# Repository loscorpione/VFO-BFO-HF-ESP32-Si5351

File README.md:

<h2 align="center">VFO/BFO con SI5351A ed ESP32</h2>

VFO & BFO con Si5351 gestito da ESP32 DevKit V1 per la gamma di frequenze HF, da 1 a 30 MHz.

## 📺 Video del progetto

<p align="center">
  
</p>

## 📋 Caratteristiche principali

- Generazione VFO e BFO indipendenti con SI5351A
- Gestione modi: AM, LSB, USB, CW
- Controllo AGC (Fast/Slow) e attenuatore (-20dB)
- Pitch BFO regolabile (±300 Hz, step 5 Hz)
- S-meter digitale con memoria di picco
- Supporto encoder ottico (400 PPR) e meccanico (24 PPR)
- Display TFT a colori (TFT_eSPI)
- Tastiera a matrice 4x4 via PCF8574T per inserimento frequenza
- Espansione I/O tramite PCF8574 (8 bit)
- Memorizzazione configurazioni su EEPROM 24LC256 (32KB)
- Firmware modulare in C++
- Calibrazione SI5351 automatica e manuale

## ✨ Novità della versione 2.1.0

Questa release introduce miglioramenti significativi nella gestione della frequenza, nell'interfaccia utente e nella calibrazione.

### 🎯 Frequenza visualizzata sempre corretta
- **IF dinamica per modalità**: la frequenza del VFO viene calcolata dinamicamente in base alla modalità selezionata (AM, LSB, USB, CW), compensando l'offset del BFO.
- **Display allineato alla stazione reale**: la frequenza mostrata sul display corrisponde sempre a quella effettiva della stazione ricevuta, senza scostamenti di 1.5 kHz.
- **Confronto diretto con altri ricevitori**: ora è possibile confrontare la frequenza visualizzata con quella di un IC-756 o di un altro apparato commerciale.

### 📻 Cambio automatico della banda laterale
- **LSB sotto 10 MHz, USB sopra 10 MHz**: al cambio banda, la modalità viene impostata automaticamente in base alla frequenza.
- **Funziona con tutte le fonti**: il cambio automatico si attiva sia cambiando banda, sia ruotando l'encoder, sia inserendo la frequenza da tastiera.
- **Rispetto delle modalità AM e CW**: se l'utente ha selezionato AM o CW, il cambio automatico non viene applicato.

### ⌨️ Miglioramenti alla tastiera 4x4
- **Limiti sui tasti `*` e `#`**: il cambio step si ferma ai limiti minimo (10 Hz) e massimo (10 kHz), evitando valori non validi.
- **Inserimento frequenza più intuitivo**: i punti separatori vengono aggiunti automaticamente dopo la 2ª e la 5ª cifra.
- **Timeout con ripristino corretto**: dopo 5 secondi di inattività, il display torna alla frequenza corrente senza lasciare la modalità input.

### 🖥️ Nuova schermata iniziale
- **Logo e informazioni di sistema**: la schermata iniziale mostra logo, versione hardware, versione firmware, autore e lista dei dispositivi I2C rilevati.
- **Rilevamento automatico EEPROM**: il sistema identifica il tipo di EEPROM (24LC32, 24LC64, 24LC128, 24LC256) in base alla dimensione configurata.

### 🔧 Calibrazione SI5351 migliorata
- **Calibrazione automatica con `CAL_FREQ`**: inserendo la frequenza misurata con un frequenzimetro, il sistema calcola e applica il fattore di correzione ottimale.
- **Calibrazione manuale con `CAL_MAN`**: per utenti esperti, è possibile impostare direttamente il fattore di correzione.
- **Istruzioni integrate**: i comandi `CAL_MAN?` e `CAL_FREQ?` mostrano le procedure passo-passo.
- **Maggiore precisione ad alta frequenza**: la calibrazione è più efficace se eseguita su frequenze elevate (es. 28 MHz).

### 🐛 Bugfix e miglioramenti
- Corretto il disallineamento di 1.5 kHz tra frequenza visualizzata e frequenza reale in LSB/USB.
- Risolto il problema del font che rimaneva ingrandito dopo un errore di inserimento frequenza.
- Corretto il salvataggio della frequenza inserita da tastiera in EEPROM.
- Migliorata la stabilità della comunicazione I2C con la EEPROM esterna.
- Rimossi i messaggi di debug ridondanti dal monitor seriale.

## 🔧 Comandi

| Comando | Descrizione |
|---------|-------------|
| **Encoder VFO** | Selezione frequenza (step 10Hz, 100Hz, 1kHz, 10kHz) |
| **Encoder BFO** | Regolazione pitch BFO (±300Hz) |
| **STEP** | Cambio step VFO |
| **BAND** | Selezione banda (160m → 10m) |
| **MODE** | Selezione demodulazione (AM/LSB/USB/CW) |
| **AGC** | Fast / Slow |
| **ATT** | Attenuatore -20dB ON/OFF |
| **Tastiera 4x4** | Inserimento diretto frequenza (0-9, A=conferma, C/#=annulla) |
| **Tasti `*` e `#`** | Step down / Step up (con limiti 10Hz-10kHz) |

## 🖥️ Comandi seriali

| Comando | Descrizione |
|---------|-------------|
| `CAL_MAN <valore>` | Imposta fattore di calibrazione manuale |
| `CAL_MAN?` | Istruzioni per la calibrazione manuale |
| `CAL_FREQ <freq>` | Calibrazione automatica (inserisci frequenza misurata) |
| `CAL_FREQ?` | Istruzioni per la calibrazione automatica |
| `CAL_READ` | Legge il fattore di calibrazione corrente |
| `CAL_RESET` | Resetta la calibrazione a 0 |
| `INFO` | Mostra informazioni di sistema |
| `HELP` | Mostra tutti i comandi disponibili |

### Esempio di calibrazione automatica

```text
> CAL_FREQ 28454710

=== CALIBRAZIONE AUTOMATICA ===
Target: 28455000 Hz
Misurato: 28454710 Hz
Errore: -290 Hz
Fattore calcolato: -10193
✅ Calibrazione automatica salvata.
```

🎬 **Guarda il video dimostrativo:**

<p align="center">
  
</p>

## 🛠️ Architettura del codice
```text
VFO-BFO HF ESP32 Code/
├── src/
│ ├── main.cpp # Loop principale e gestione comandi seriale
│ ├── config.h # Pin, parametri e versioni
│ ├── display.cpp/h # Gestione display TFT e splash screen
│ ├── VFO_BFO.cpp/h # Gestione encoder VFO/BFO
│ ├── PLL.cpp/h # Configurazione SI5351
│ ├── bands.cpp/h # Gestione bande
│ ├── modes.cpp/h # Gestione modalità (AM/LSB/USB/CW)
│ ├── DigiOUT.cpp/h # Uscite digitali PCF8574
│ ├── s_meter.cpp/h # S-meter analogico
│ ├── functions.cpp/h # Gestione pulsanti AGC/ATT
│ ├── keypad.cpp/h # Gestione tastiera 4x4
│ └── EEPROM_manager.cpp/h # Memorizzazione configurazioni
└── platformio.ini # Configurazione PlatformIO
```

## 🔌 Collegamenti principali
```text
| Componente | Pin ESP32 |
|------------|-----------|
| VFO Encoder CLK | 34 |
| VFO Encoder DT | 35 |
| BFO Encoder CLK | 12 |
| BFO Encoder DT | 13 |
| STEP | 32 |
| BAND | 33 |
| MODE | 25 |
| AGC | 26 |
| ATT | 27 |
| I2C SDA | 21 |
| I2C SCL | 22 |
| S-Meter | 15 (ADC) |
```

## 📦 Dipendenze (platformio.ini)
```text
lib_deps = 
    bodmer/TFT_eSPI@^2.5.0
    madhephaestus/ESP32Encoder@^0.12.0
    robtillaart/PCF8574@^0.4.4
    robtillaart/I2CKeyPad@^0.5.2
```
## 📜 Licenza

MIT

## 👤 Autore

Scorpione Maker - IV3LDJ

GitHub: loscorpione

YouTube: @ScorpioneMaker

## ⭐ Se questo progetto ti è utile, lascia una stella su GitHub!

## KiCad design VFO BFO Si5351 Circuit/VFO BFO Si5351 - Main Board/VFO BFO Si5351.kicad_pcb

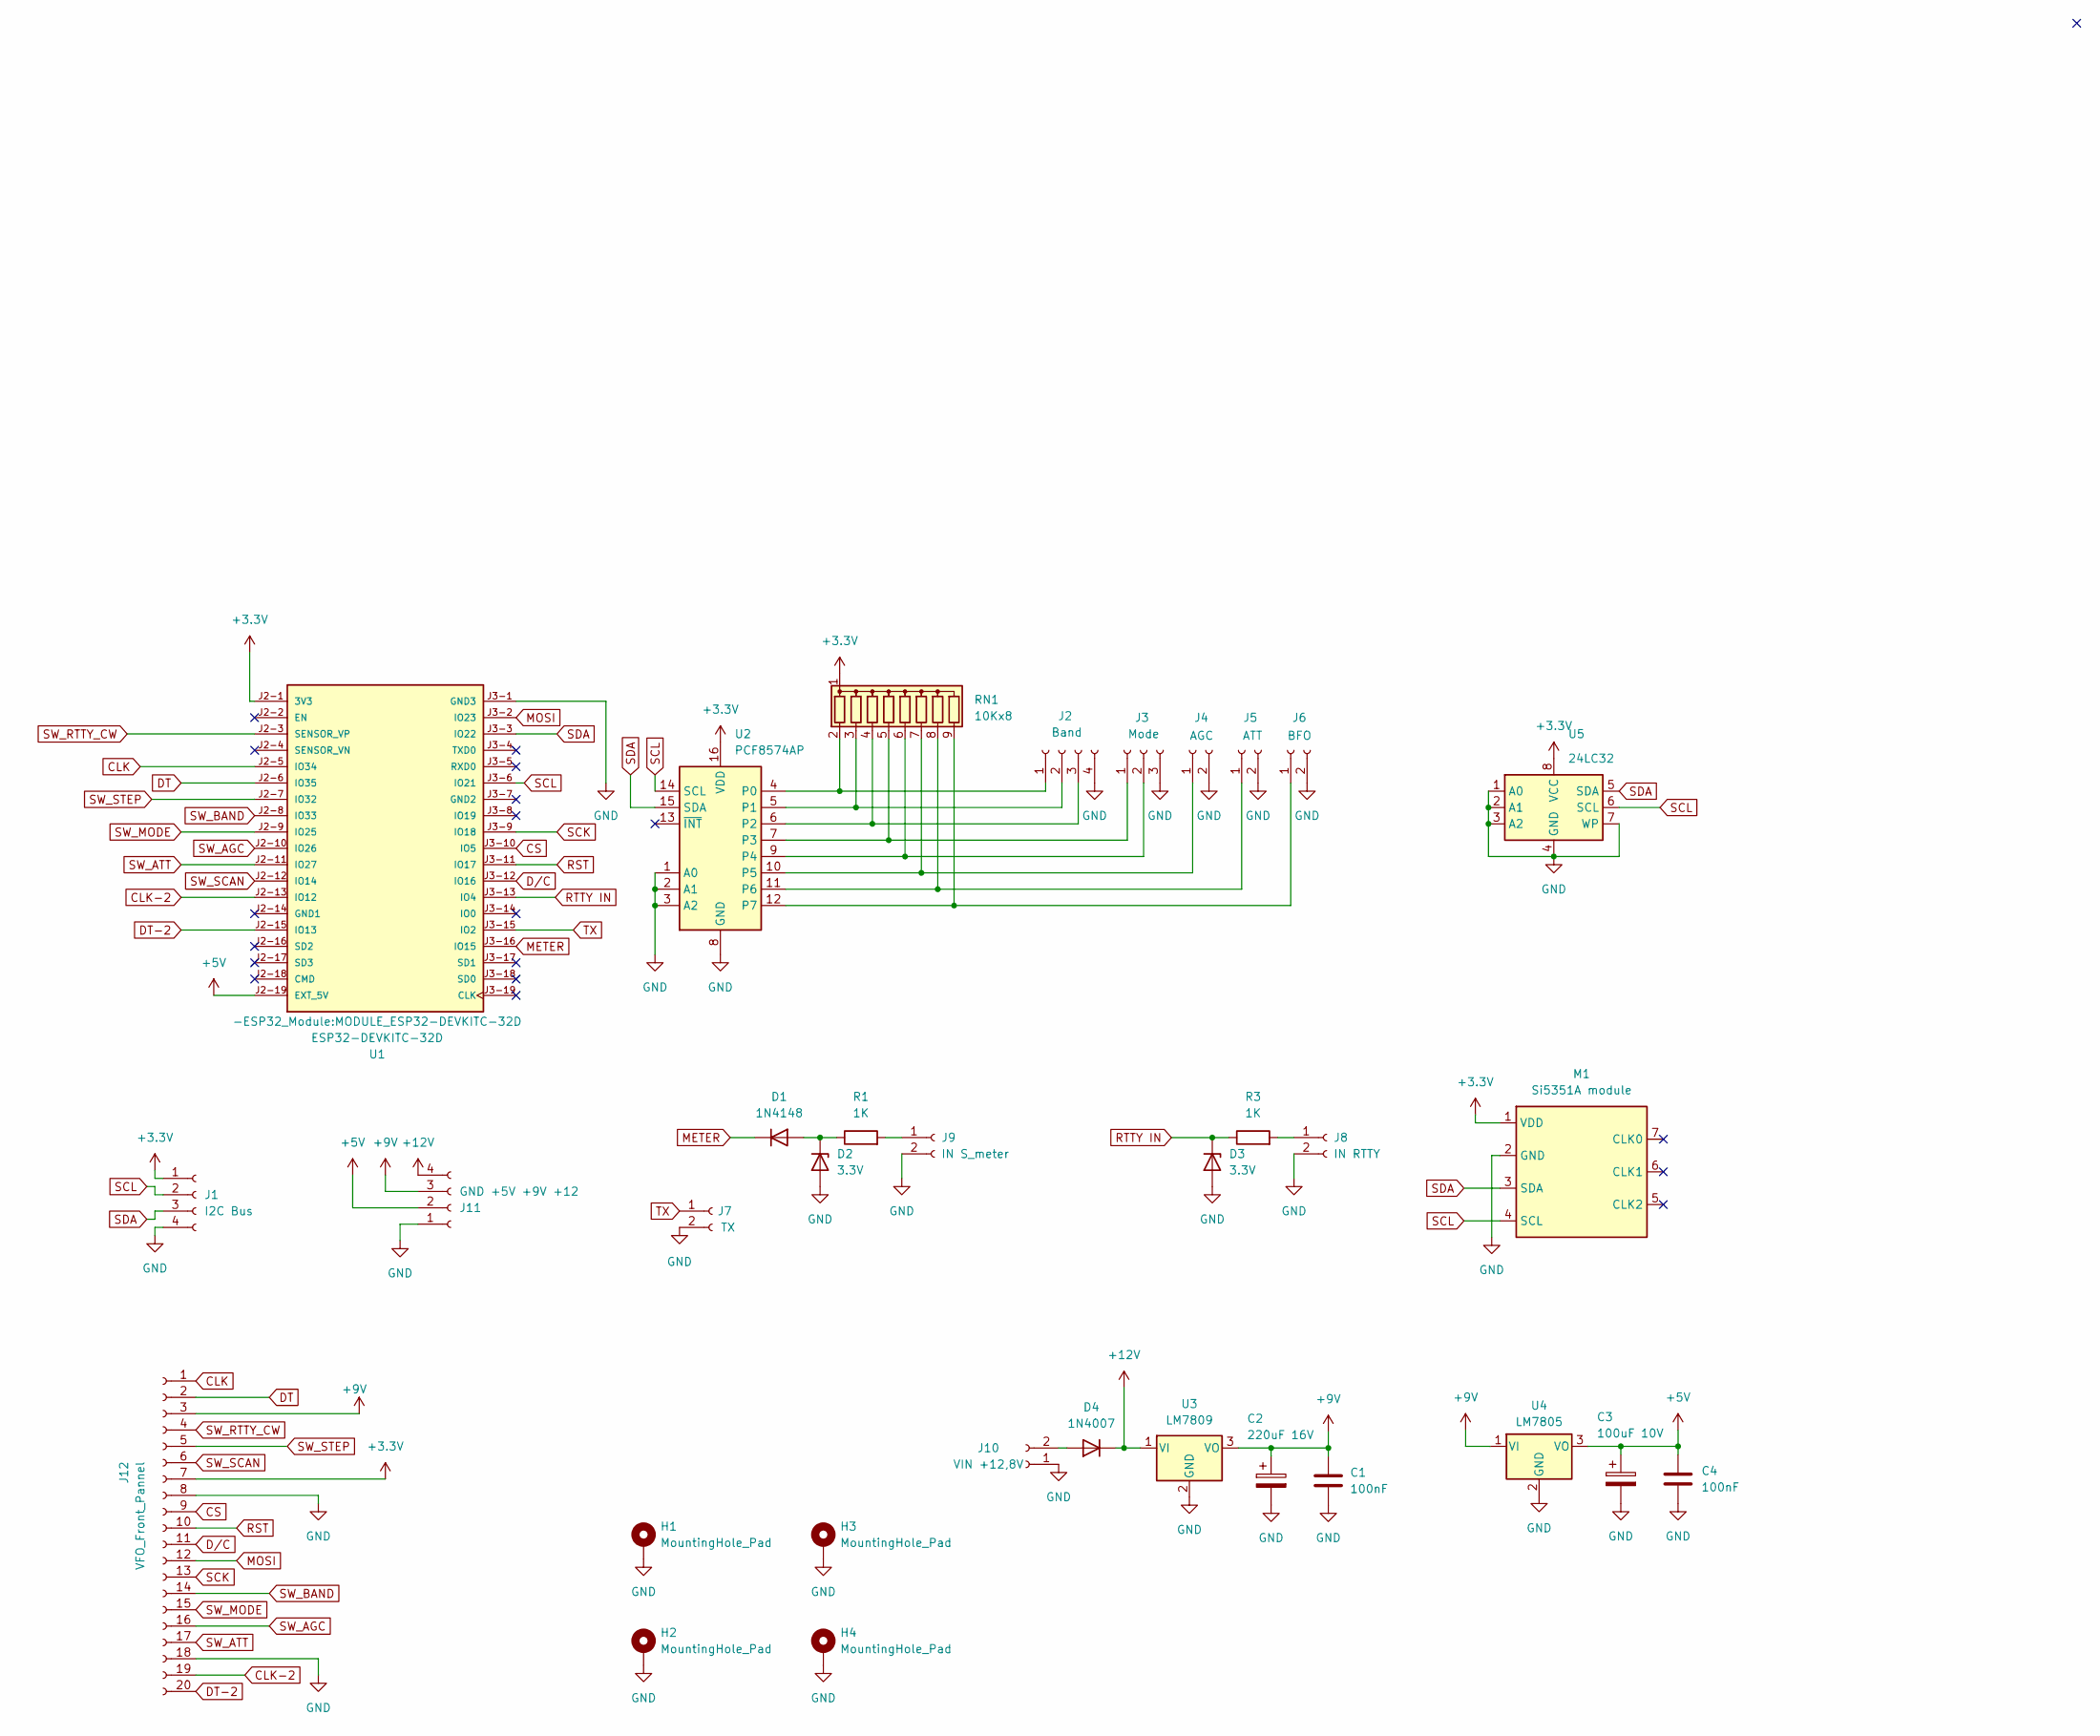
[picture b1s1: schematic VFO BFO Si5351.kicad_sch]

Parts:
C1, C4: 100nF; C_Rect_L7.0mm_W2.5mm_P5.00mm
C2: 220uF 16V; CP_Radial_D6.3mm_P2.50mm
C3: 100uF 10V; CP_Radial_D5.0mm_P2.00mm
D1: 1N4148; D_DO-35_SOD27_P7.62mm_Horizontal
D2, D3: 3.3V; D_DO-35_SOD27_P7.62mm_Horizontal
D4: 1N4007; D_DO-41_SOD81_P10.16mm_Horizontal
H1, H2, H3, H4: MountingHole_Pad; MountingHole_3.2mm_M3_DIN965_Pad_TopBottom
J1: I2C Bus; JST_EH_B4B-EH-A_1x04_P2.50mm_Vertical
J2: Band; JST_EH_B4B-EH-A_1x04_P2.50mm_Vertical
J3: Mode; JST_EH_B3B-EH-A_1x03_P2.50mm_Vertical
J4: AGC; JST_EH_B2B-EH-A_1x02_P2.50mm_Vertical
J5: ATT; JST_EH_B2B-EH-A_1x02_P2.50mm_Vertical
J6: BFO; JST_EH_B2B-EH-A_1x02_P2.50mm_Vertical
J7: TX; JST_EH_B2B-EH-A_1x02_P2.50mm_Vertical
J8: IN RTTY; JST_EH_B2B-EH-A_1x02_P2.50mm_Vertical
J9: IN S_meter; JST_EH_B2B-EH-A_1x02_P2.50mm_Vertical
J10: VIN +12,8V; JST_EH_B2B-EH-A_1x02_P2.50mm_Vertical
J11: GND +5V +9V +12; JST_EH_B4B-EH-A_1x04_P2.50mm_Vertical
J12: VFO_Front_Pannel; PinHeader_1x20_P2.54mm_Vertical
M1: Si5351A module; si5351a_Module
R1, R3: 1K; R_Axial_DIN0207_L6.3mm_D2.5mm_P10.16mm_Horizontal
RN1: 10Kx8; R_Array_SIP9
U1: ESP32-DEVKITC-32D; MODULE_ESP32-DEVKITC-32D; PARTREV V4
U2: PCF8574AP; DIP-16_W7.62mm
U3: LM7809; TO-220-3_Vertical
U4: LM7805; TO-220-3_Vertical
U5: 24LC32; DIP-8_W7.62mm

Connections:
+3.3V: J1.1, J12.7, M1.1 (VDD), RN1.1 (common), U1.J2-1 (3V3), U2.16 (VDD), U5.8 (VCC)
+5V: C3.1, C4.1, J11.2, U1.J2-19 (EXT_5V), U4.3 (VO)
+9V: C1.1, C2.1, J11.3, J12.3, U3.3 (VO), U4.1 (VI)
+12V: D4.1 (K), J11.4, U3.1 (VI)
CLK: J12.1, U1.J2-5 (IO34)
CLK-2: J12.19, U1.J2-13 (IO12)
CS: J12.9, U1.J3-10 (IO5)
DT: J12.2, U1.J2-6 (IO35)
DT-2: J12.20, U1.J2-15 (IO13)
D/C: J12.11, U1.J3-12 (IO16)
GND: C1.2, C2.2, C3.2, C4.2, D2.2 (A), D3.2 (A), H1.1, H2.1, H3.1, H4.1, J1.4, J2.4, J3.3, J4.2, J5.2, J6.2, J7.2, J8.2, J9.2, J10.1, J11.1, J12.8, J12.18, M1.2 (GND), U1.J3-1 (GND3), U2.1 (A0), U2.2 (A1), U2.3 (A2), U2.8 (GND), U3.2 (GND), U4.2 (GND), U5.1 (A0), U5.2 (A1), U5.3 (A2), U5.4 (GND), U5.7 (WP)
METER: D1.1 (K), U1.J3-16 (IO15)
MOSI: J12.12, U1.J3-2 (IO23)
unnamed: D1.2 (A), D2.1 (K), R1.1
unnamed: D4.2 (A), J10.2
unnamed: J2.1, RN1.2 (R1), U2.4 (P0)
unnamed: J2.2, RN1.3 (R2), U2.5 (P1)
unnamed: J2.3, RN1.4 (R3), U2.6 (P2)
unnamed: J3.1, RN1.5 (R4), U2.7 (P3)
unnamed: J3.2, RN1.6 (R5), U2.9 (P4)
unnamed: J4.1, RN1.7 (R6), U2.10 (P5)
unnamed: J5.1, RN1.8 (R7), U2.11 (P6)
unnamed: J6.1, RN1.9 (R8), U2.12 (P7)
unnamed: J8.1, R3.2
unnamed: J9.1, R1.2
RST: J12.10, U1.J3-11 (IO17)
RTTY IN: D3.1 (K), R3.1, U1.J3-13 (IO4)
SCK: J12.13, U1.J3-9 (IO18)
SCL: J1.2, M1.4 (SCL), U1.J3-6 (IO21), U2.14 (SCL), U5.6 (SCL)
SDA: J1.3, M1.3 (SDA), U1.J3-3 (IO22), U2.15 (SDA), U5.5 (SDA)
SW_AGC: J12.16, U1.J2-10 (IO26)
SW_ATT: J12.17, U1.J2-11 (IO27)
SW_BAND: J12.14, U1.J2-8 (IO33)
SW_MODE: J12.15, U1.J2-9 (IO25)
SW_RTTY_CW: J12.4, U1.J2-3 (SENSOR_VP)
SW_SCAN: J12.6, U1.J2-12 (IO14)
SW_STEP: J12.5, U1.J2-7 (IO32)
TX: J7.1, U1.J3-15 (IO2)

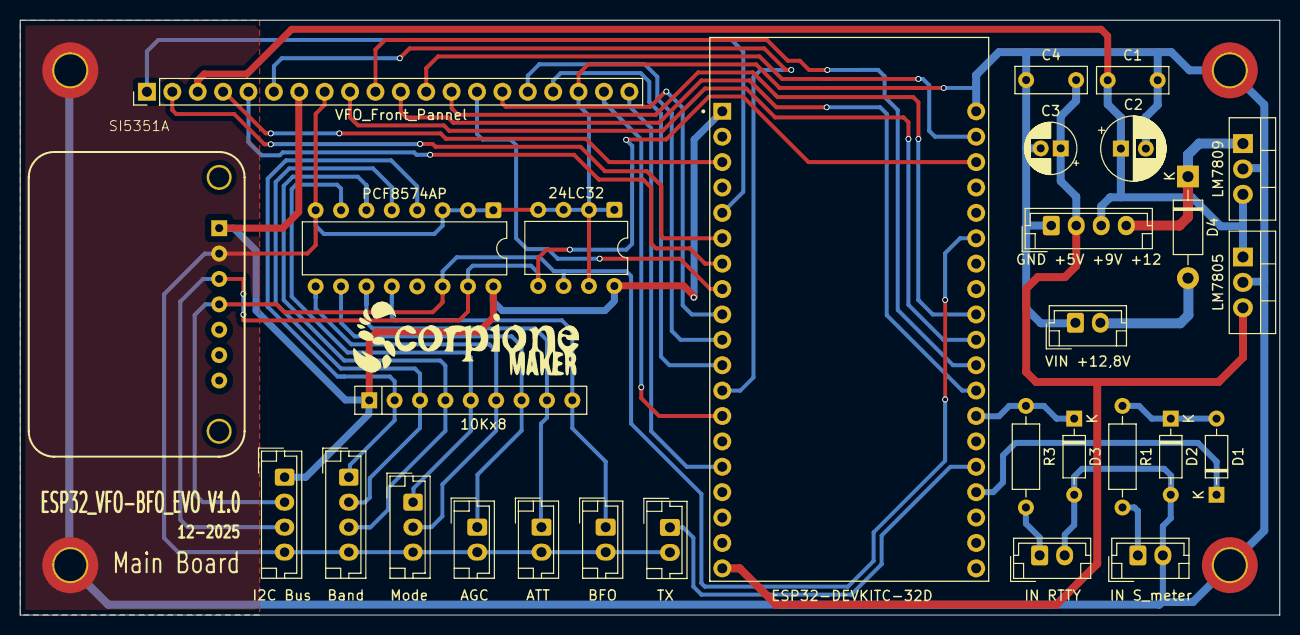
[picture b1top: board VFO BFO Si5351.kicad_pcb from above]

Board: 2 copper layers, 126.0 x 59.5 mm, 33 parts (0 on the bottom side), 38 nets.

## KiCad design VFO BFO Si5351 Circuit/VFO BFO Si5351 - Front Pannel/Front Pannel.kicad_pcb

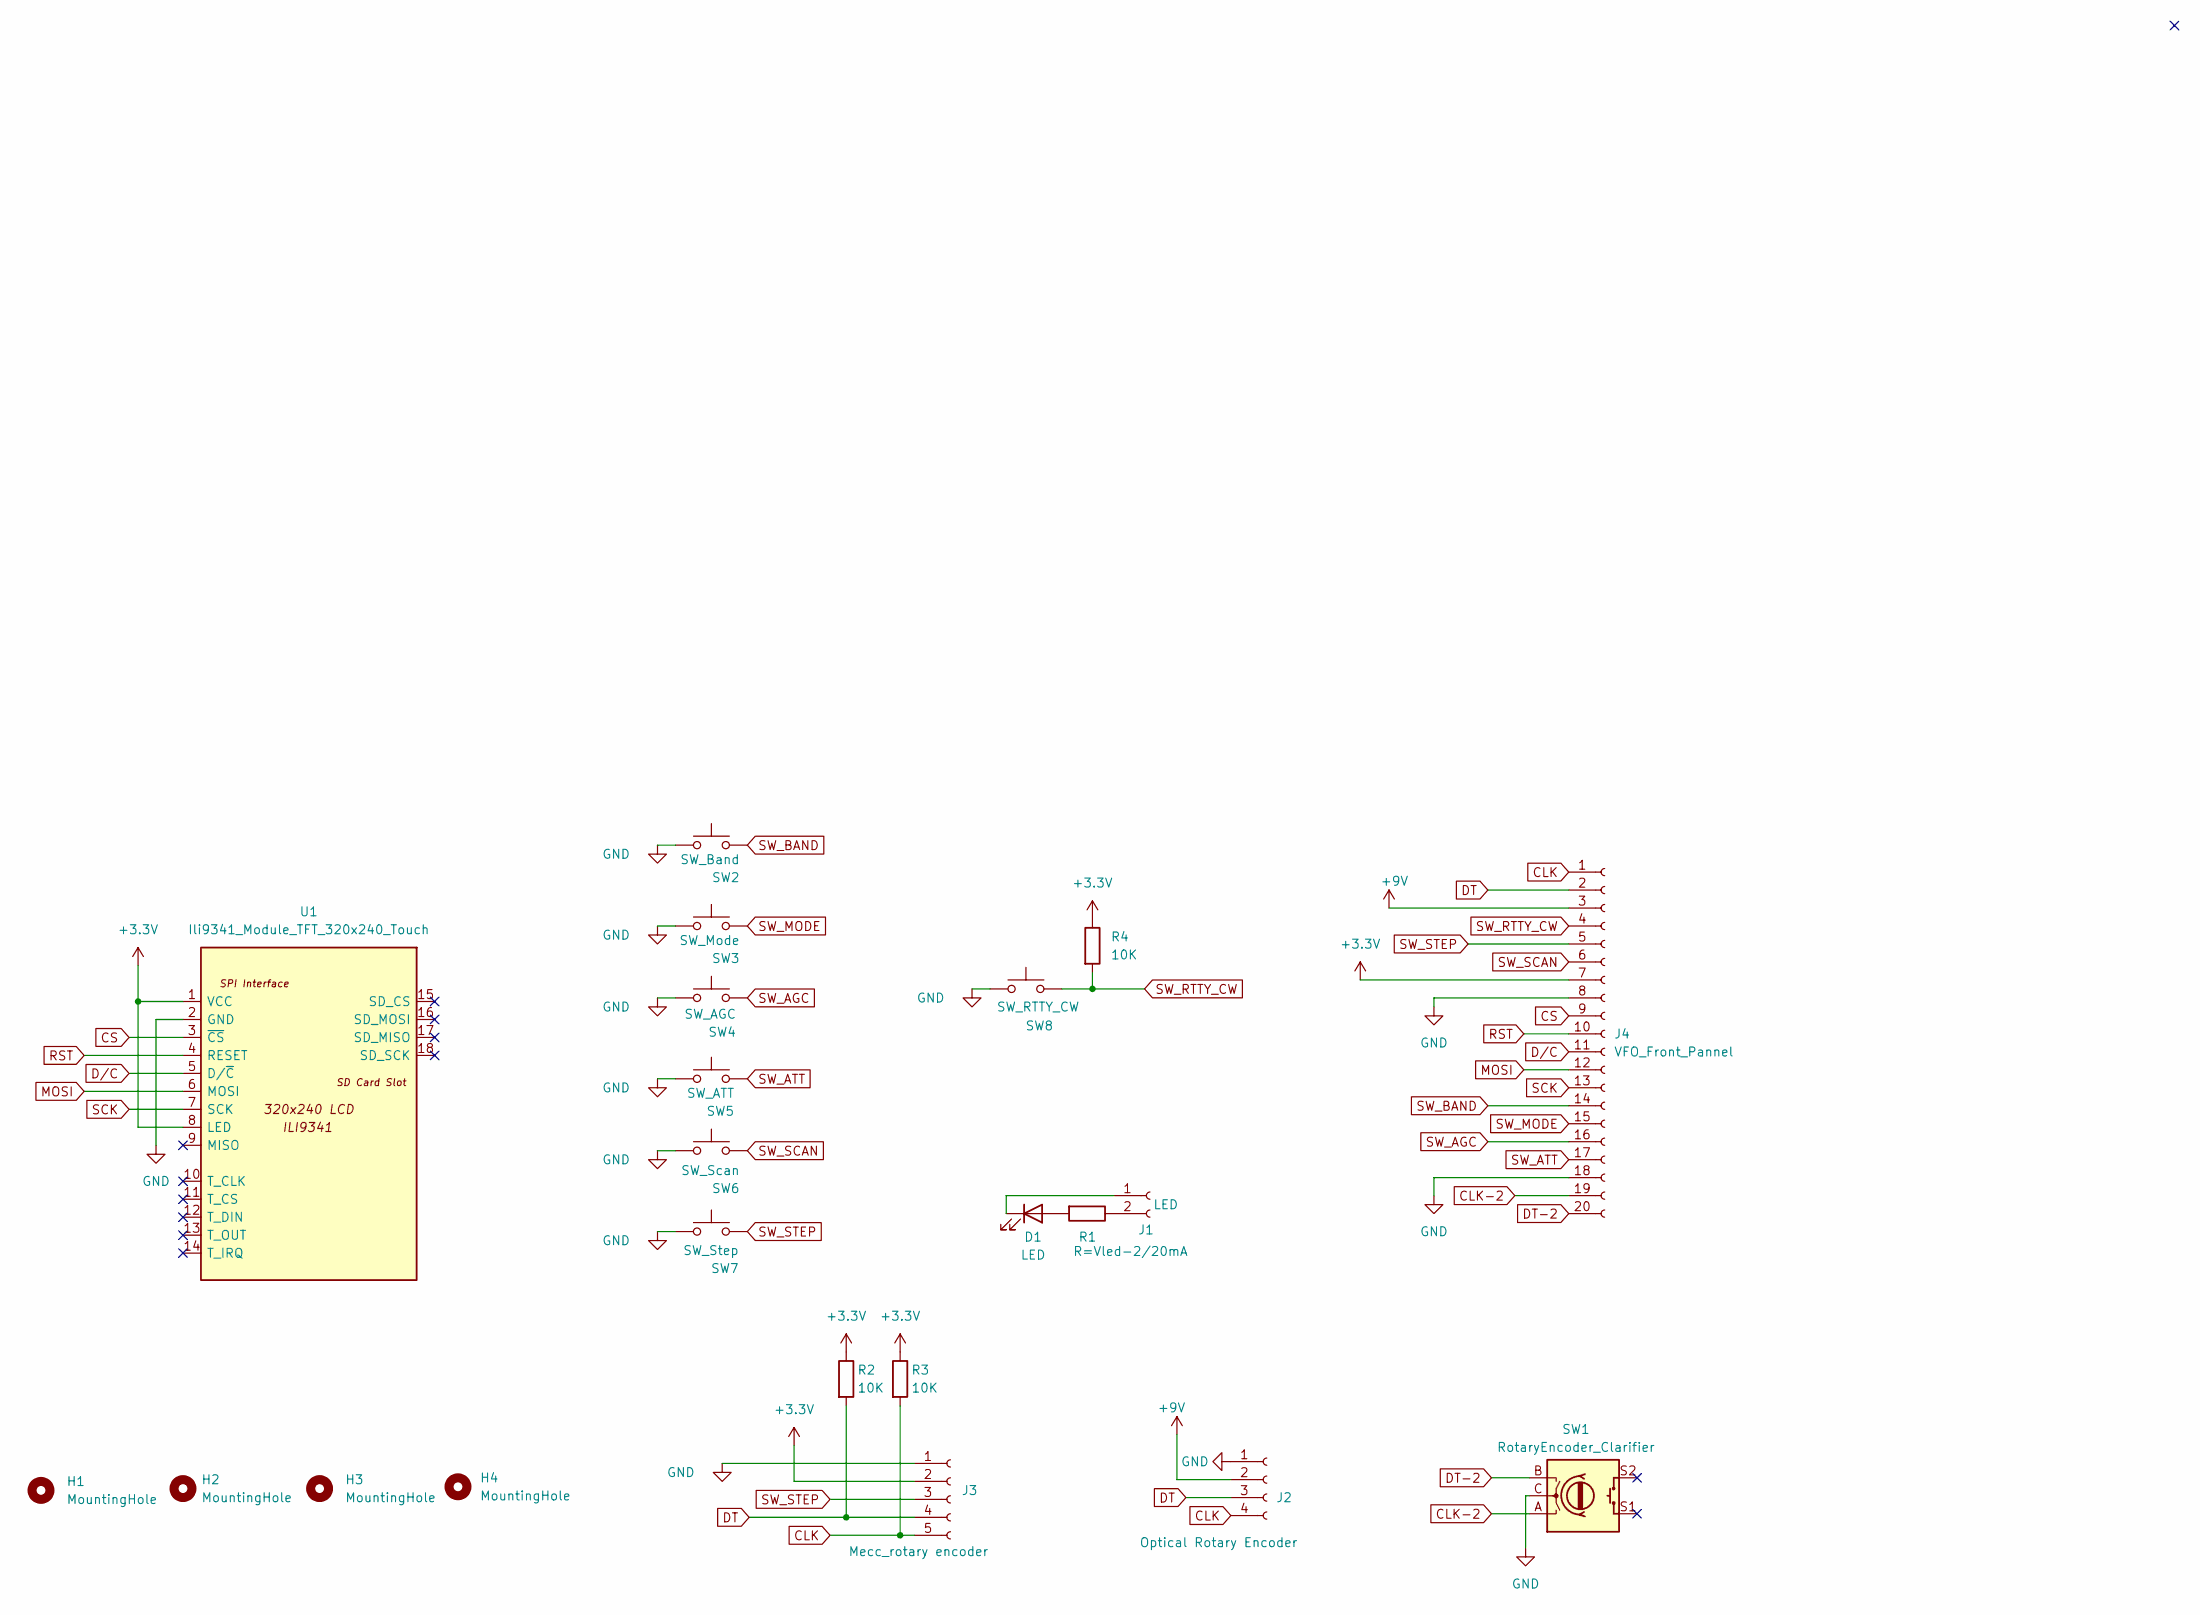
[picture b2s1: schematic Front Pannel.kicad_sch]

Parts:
D1: LED; LED_D3.0mm
H1, H2, H3, H4: MountingHole; MountingHole_3.2mm_M3_DIN965
J1: LED; JST_EH_B2B-EH-A_1x02_P2.50mm_Vertical
J2: Optical Rotary Encoder; JST_EH_B4B-EH-A_1x04_P2.50mm_Vertical
J3: Mecc_rotary encoder; PinSocket_1x05_P2.54mm_Horizontal
J4: VFO_Front_Pannel; PinHeader_1x20_P2.54mm_Vertical
R1: R=Vled-2/20mA; R_Axial_DIN0207_L6.3mm_D2.5mm_P10.16mm_Horizontal
R2, R3, R4: 10K; R_Axial_DIN0207_L6.3mm_D2.5mm_P10.16mm_Horizontal
SW1: RotaryEncoder_Clarifier; RotaryEncoder_Alps_EC12E-Switch_Vertical_H20mm
SW2: SW_Band; SW_PUSH_6mm
SW3: SW_Mode; SW_PUSH_6mm
SW4: SW_AGC; SW_PUSH_6mm
SW5: SW_ATT; SW_PUSH_6mm
SW6: SW_Scan; SW_PUSH_6mm
SW7: SW_Step; SW_PUSH_6mm
SW8: SW_RTTY_CW; SW_PUSH_6mm
U1: Ili9341_Module_TFT_320x240_Touch; DISPLAY_TFT_ILI9341_2.8

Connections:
+3.3V: J3.2, J4.7, R2.1, R3.1, R4.1, U1.1 (VCC), U1.8 (LED)
+9V: J2.2, J4.3
CLK: J2.4, J3.5, J4.1, R3.2
CLK-2: J4.19, SW1.A
CS: J4.9, U1.3 (~CS)
DT: J2.3, J3.4, J4.2, R2.2
DT-2: J4.20, SW1.B
D/C: J4.11, U1.5 (D/~C)
GND: J2.1, J3.1, J4.8, J4.18, SW1.C, SW2.1, SW3.1, SW4.1, SW5.1, SW6.1, SW7.1, SW8.1, U1.2 (GND)
MOSI: J4.12, U1.6 (MOSI)
unnamed: D1.2 (A), R1.2
unnamed: D1.1 (K), J1.1
unnamed: J1.2, R1.1
RST: J4.10, U1.4 (RESET)
SCK: J4.13, U1.7 (SCK)
SW_AGC: J4.16, SW4.2
SW_ATT: J4.17, SW5.2
SW_BAND: J4.14, SW2.2
SW_MODE: J4.15, SW3.2
SW_RTTY_CW: J4.4, R4.2, SW8.2
SW_SCAN: J4.6, SW6.2
SW_STEP: J3.3, J4.5, SW7.2

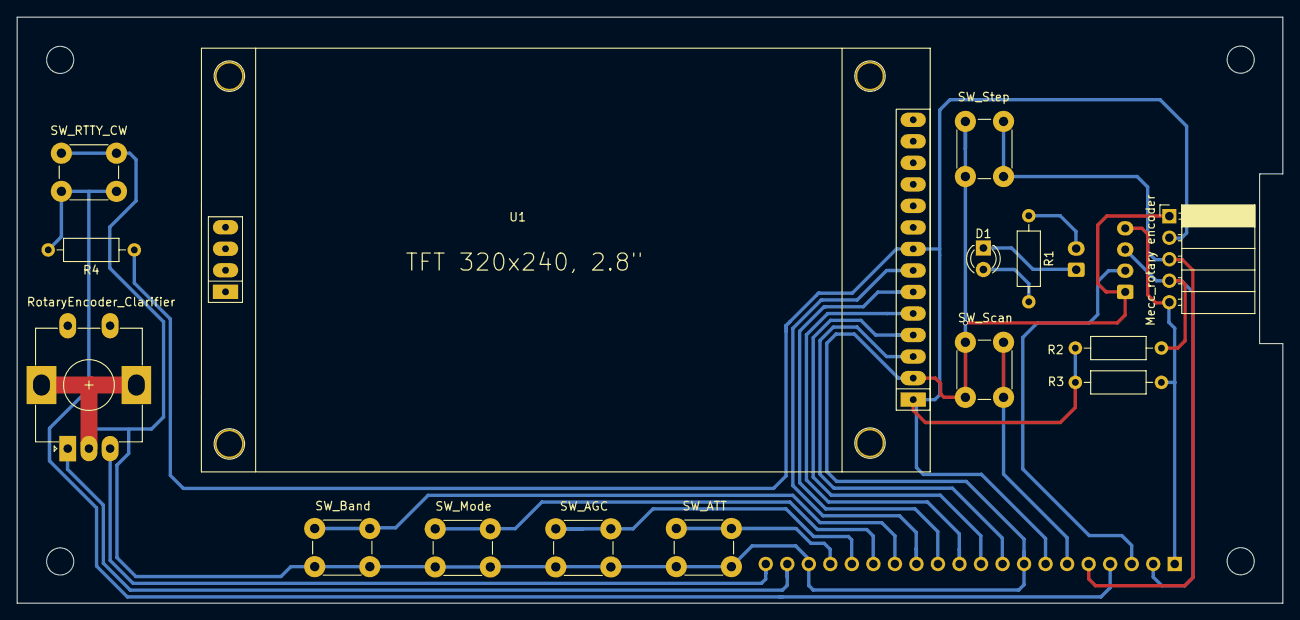
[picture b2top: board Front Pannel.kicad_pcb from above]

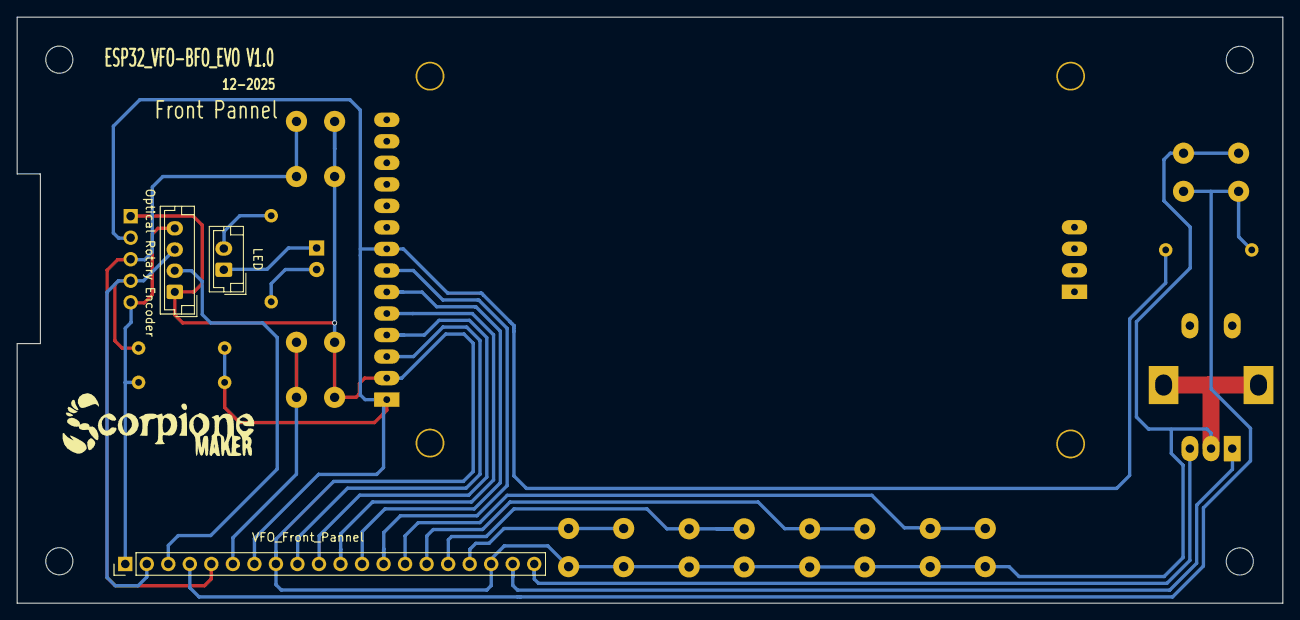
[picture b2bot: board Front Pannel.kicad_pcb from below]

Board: 2 copper layers, 149.4 x 69.2 mm, 22 parts (3 on the bottom side), 22 nets.

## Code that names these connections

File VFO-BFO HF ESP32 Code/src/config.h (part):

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    // CONFIGURAZIONE PULSANTI
    // ============================================

        #define SW_STEP 32                  // Pulsante cambio Step VFO
        #define SW_BAND 33                  // Pulsante cambio banda
        #define SW_MODE 25                  // Pulsante cambio modalità
        #define SW_AGC  26                  // Pulsante AGC Fast/Slow
        #define SW_ATT  27                  // Pulsante Attenuatore -20dB
        #define SW_SCAN 14                  // Pulsante blocco frequenza (ex SW_SCAN)
        #define SW_RTTY_CW  36              // Pulsante RTTY_CW (futuro)

        // Debounce per tutti i pulsanti
        const int buttonDebounce = 200;
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    // CONFIGURAZIONE INPUT/OUTPUT VARI
    // ============================================

        // Configurazione GPIO Ingresso S-Meter 
        #define S_METER_PIN 15              // Pin analogico per il S-meter
            
        // Configurazione GPIO Ingresso RTTY_CW 
        #define RTTY_CW_PIN 4               // Pin digitale per RTTY_CW (futuro)
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
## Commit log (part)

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2026-01-16 ultimato PCB
2026-02-07 Mod code end PCB
    Schema elettrico Main-board and Front-panel correzione impronta SI5351 e PCB
    Pulizia Codice ed implementazione out digitale BFO
2026-02-13 Modifiche al PCB
2026-02-17 Enhance README with project details and features
    Updated README to provide detailed project description and features.
2026-02-17 Add video section to README
    Added a video section with a link and thumbnail.

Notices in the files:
README.md:
License: MIT
